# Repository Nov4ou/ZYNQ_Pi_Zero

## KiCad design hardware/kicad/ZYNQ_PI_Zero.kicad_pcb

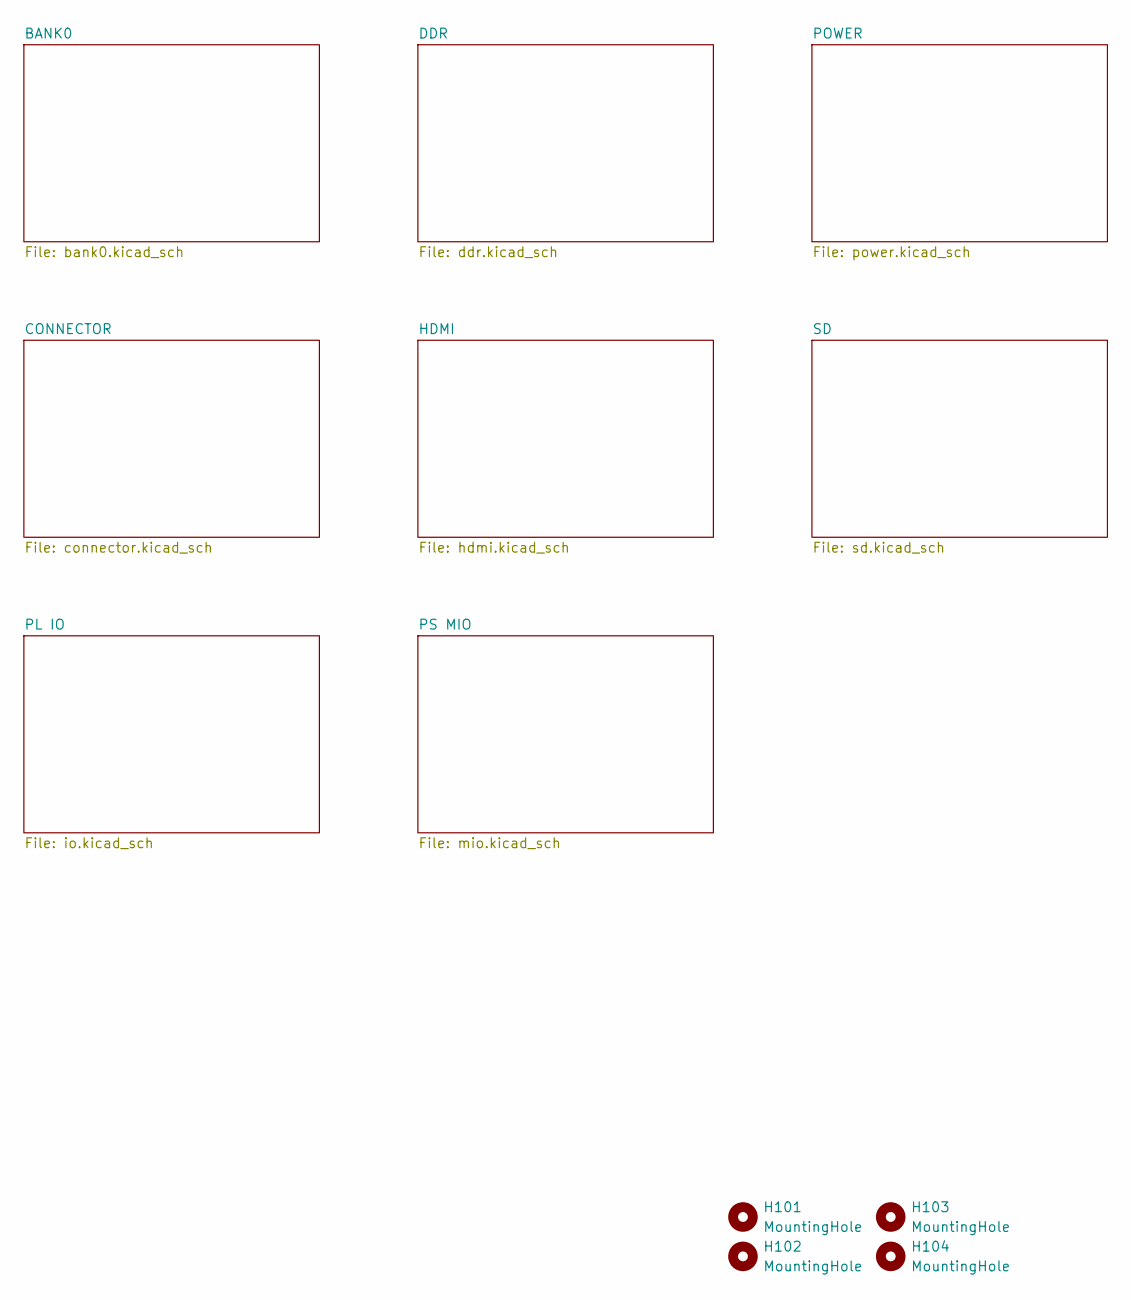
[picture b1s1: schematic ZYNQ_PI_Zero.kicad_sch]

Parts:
H101, H102, H103, H104: MountingHole; MountingHole_3.2mm_M3

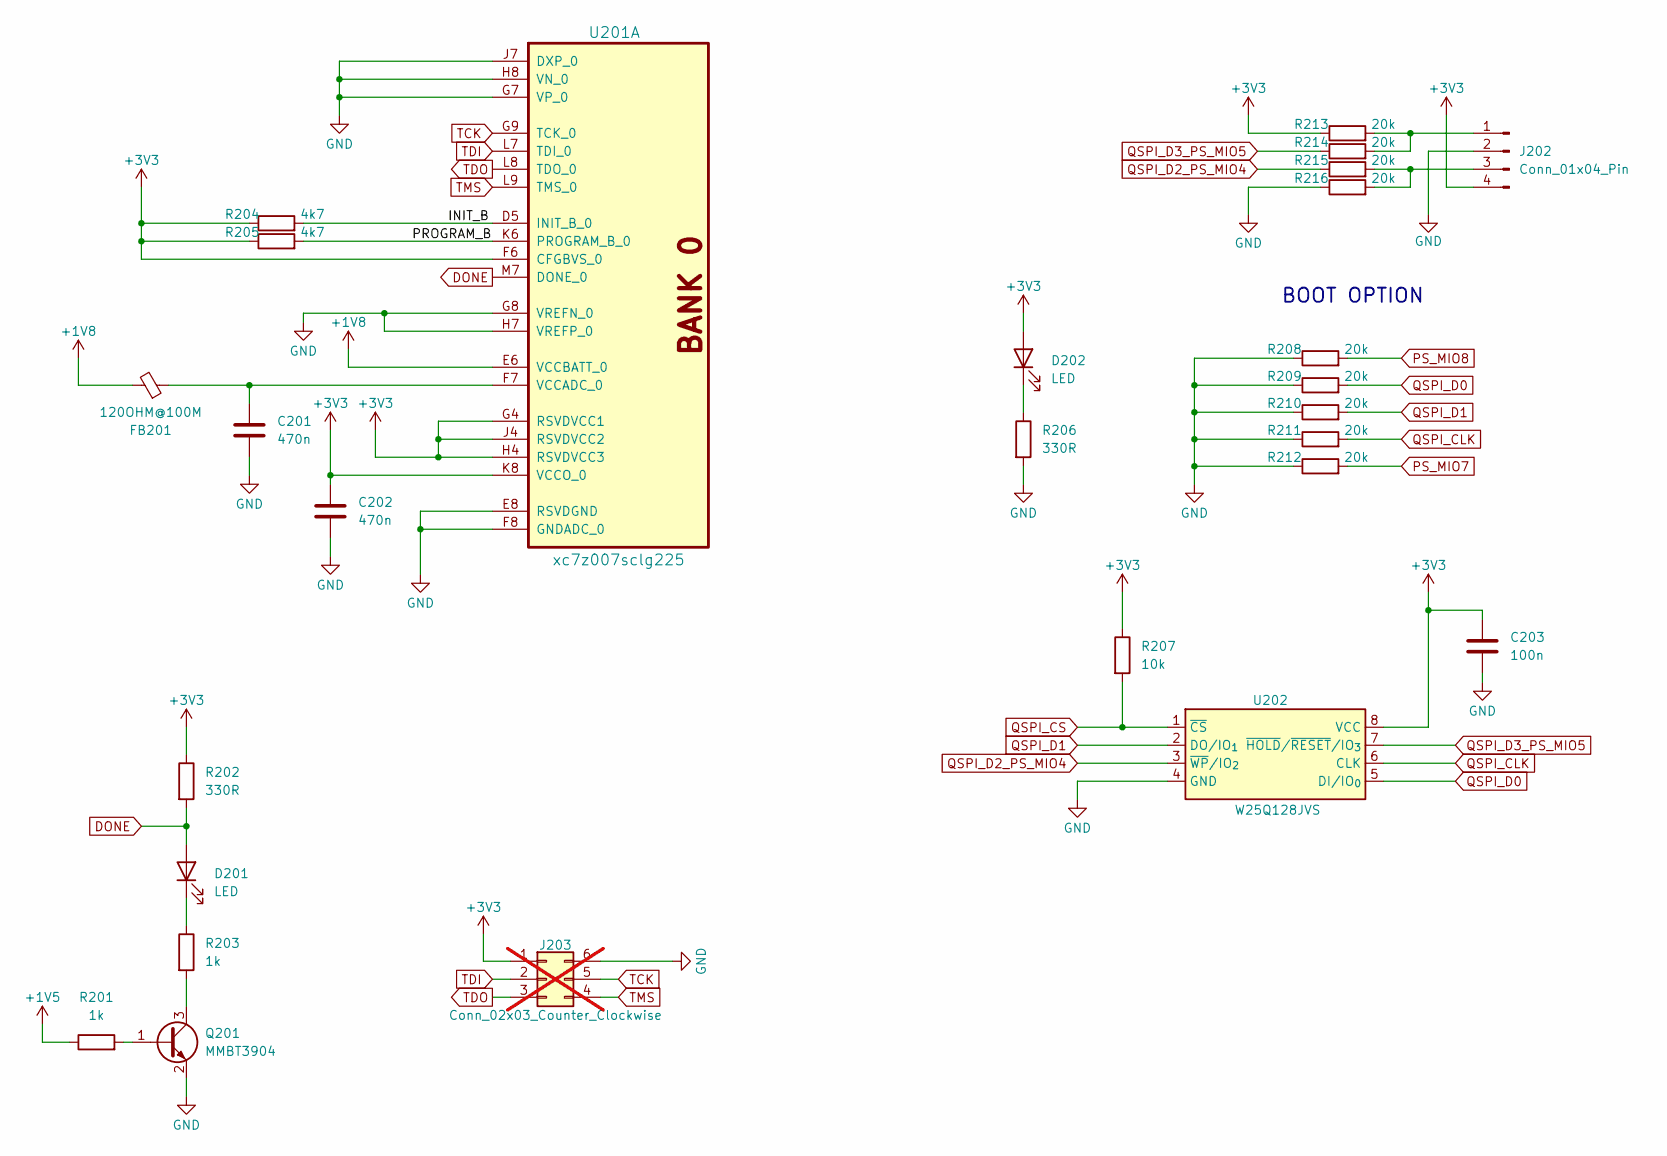
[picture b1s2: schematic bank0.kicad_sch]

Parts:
C201, C202: 470n; C_0402_1005Metric
C203: 100n; C_0402_1005Metric
D201, D202: LED; LED_0603_1608Metric
FB201: 120OHM@100M; L_0402_1005Metric
J202: Conn_01x04_Pin; PinHeader_1x04_P2.54mm_Vertical
J203: Conn_02x03_Counter_Clockwise; PinHeader_2x03_P2.00mm_Vertical; not fitted
Q201: MMBT3904; SOT-23
R201, R203: 1k; R_0402_1005Metric
R202, R206: 330R; R_0603_1608Metric
R204, R205: 4k7; R_0402_1005Metric
R207: 10k; R_0603_1608Metric
R208, R209, R210, R211, R212, R213, R214, R215, R216: 20k; R_0402_1005Metric
U201: xc7z007sclg225; Xilinx_CLG225
U202: W25Q128JVS; SOIC-8_5.3x5.3mm_P1.27mm

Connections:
+1V5: R201.1; also elsewhere on the board
+1V8: FB201.2, U201.E6 (VCCBATT_0); also elsewhere on the board
+3V3: C202.1, C203.1, D202.2 (A), J202.4, J203.1, R202.1, R204.1, R205.1, R207.1, R213.1, U201.F6 (CFGBVS_0), U201.G4 (RSVDVCC1), U201.H4 (RSVDVCC3), U201.J4 (RSVDVCC2), U201.K8 (VCCO_0), U202.8 (VCC); also elsewhere on the board
/BANK0/INIT_B: R204.2, U201.D5 (INIT_B_0)
/BANK0/PROGRAM_B: R205.2, U201.K6 (PROGRAM_B_0)
DONE: D201.2 (A), R202.2, U201.M7 (DONE_0)
GND: C201.2, C202.2, C203.2, J202.2, J203.6, Q201.2 (E), R206.2, R208.1, R209.1, R210.1, R211.1, R212.1, R216.1, U201.E8 (RSVDGND), U201.F8 (GNDADC_0), U201.G7 (VP_0), U201.G8 (VREFN_0), U201.H7 (VREFP_0), U201.H8 (VN_0), U201.J7 (DXP_0), U202.4 (GND); also elsewhere on the board
unnamed: D201.1 (K), R203.1
unnamed: D202.1 (K), R206.1
unnamed: J202.1, R213.2, R214.2
unnamed: J202.3, R215.2, R216.2
unnamed: Q201.1 (B), R201.2
unnamed: Q201.3 (C), R203.2
unnamed: C201.1, FB201.1, U201.F7 (VCCADC_0)
PS_MIO7: R212.2; also elsewhere on the board
PS_MIO8: R208.2; also elsewhere on the board
QSPI_CLK: R211.2, U202.6 (CLK); also elsewhere on the board
QSPI_CS: R207.2, U202.1 (~CS); also elsewhere on the board
QSPI_D0: R209.2, U202.5 (DI/IO_{0}); also elsewhere on the board
QSPI_D1: R210.2, U202.2 (DO/IO_{1}); also elsewhere on the board
QSPI_D2_PS_MIO4: R215.1, U202.3 (~WP/IO_{2}); also elsewhere on the board
QSPI_D3_PS_MIO5: R214.1, U202.7 (~HOLD/~RESET/IO_{3}); also elsewhere on the board
TCK: J203.5, U201.G9 (TCK_0)
TDI: J203.2, U201.L7 (TDI_0)
TDO: J203.3, U201.L8 (TDO_0)
TMS: J203.4, U201.L9 (TMS_0)

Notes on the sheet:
BOOT OPTION

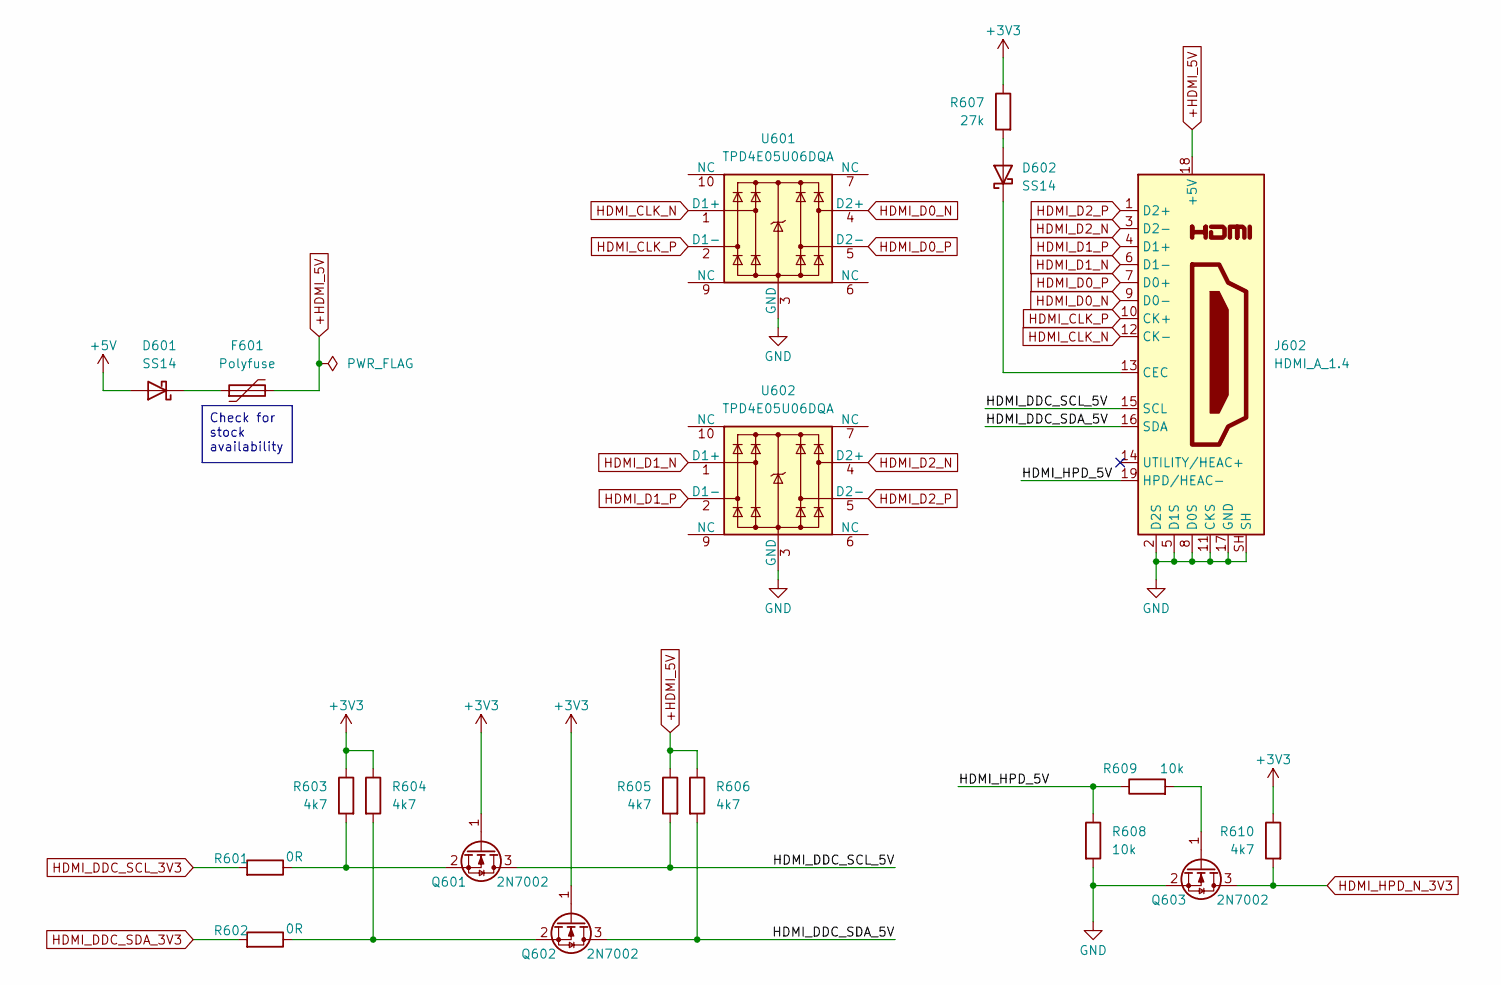
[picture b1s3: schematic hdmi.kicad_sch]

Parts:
D601, D602: SS14; D_SMA
F601: Polyfuse; Fuse_0805_2012Metric
J602: HDMI_A_1.4; HDMI-SMD_HDMI-19PIN-043_C2858275
Q601, Q602, Q603: 2N7002; SOT-23
R601, R602: 0R; R_0402_1005Metric
R603, R604, R605, R606, R610: 4k7; R_0402_1005Metric
R607: 27k; R_0603_1608Metric
R608, R609: 10k; R_0603_1608Metric
U601, U602: TPD4E05U06DQA; USON-10_2.5x1.0mm_P0.5mm

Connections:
+3V3: Q601.1 (G), Q602.1 (G), R603.1, R604.1, R607.1, R610.1; also elsewhere on the board
+5V: D601.2 (A); also elsewhere on the board
+HDMI_5V: F601.2, J602.18 (+5V), R605.1, R606.1
/HDMI/HDMI_DDC_SCL_5V: J602.15 (SCL), Q601.3 (D), R605.2
/HDMI/HDMI_DDC_SDA_5V: J602.16 (SDA), Q602.3 (D), R606.2
/HDMI/HDMI_HPD_5V: J602.19 (HPD/HEAC-), R608.1, R609.1
GND: J602.2 (D2S), J602.5 (D1S), J602.8 (D0S), J602.11 (CKS), J602.17 (GND), J602.SH, Q603.2 (S), R608.2, U601.3 (GND), U601.8 (GND), U602.3 (GND), U602.8 (GND); also elsewhere on the board
HDMI_CLK_N: J602.12 (CK-), U601.1 (D1+); also elsewhere on the board
HDMI_CLK_P: J602.10 (CK+), U601.2 (D1-); also elsewhere on the board
HDMI_D0_N: J602.9 (D0-), U601.4 (D2+); also elsewhere on the board
HDMI_D0_P: J602.7 (D0+), U601.5 (D2-); also elsewhere on the board
HDMI_D1_N: J602.6 (D1-), U602.1 (D1+); also elsewhere on the board
HDMI_D1_P: J602.4 (D1+), U602.2 (D1-); also elsewhere on the board
HDMI_D2_N: J602.3 (D2-), U602.4 (D2+); also elsewhere on the board
HDMI_D2_P: J602.1 (D2+), U602.5 (D2-); also elsewhere on the board
HDMI_DDC_SCL_3V3: R601.2; also elsewhere on the board
HDMI_DDC_SDA_3V3: R602.2; also elsewhere on the board
HDMI_HPD_N_3V3: Q603.3 (D), R610.2; also elsewhere on the board
unnamed: D601.1 (K), F601.1
unnamed: D602.2 (A), R607.2
unnamed: D602.1 (K), J602.13 (CEC)
unnamed: Q601.2 (S), R601.1, R603.2
unnamed: Q602.2 (S), R602.1, R604.2
unnamed: Q603.1 (G), R609.2

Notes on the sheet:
Check for stock availability

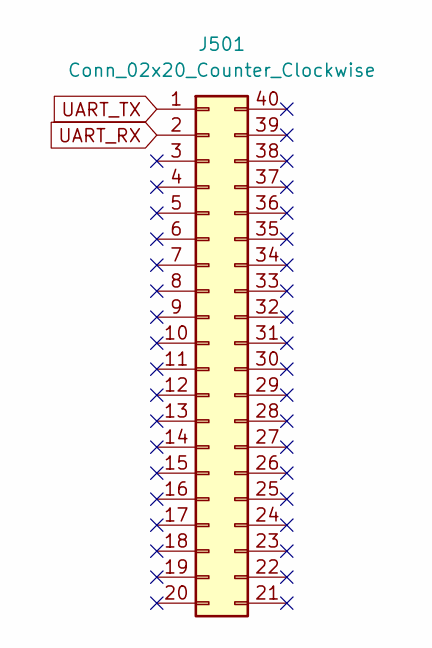
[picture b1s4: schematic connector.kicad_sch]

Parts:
J501: Conn_02x20_Counter_Clockwise; PinHeader_2x20_P2.54mm_Vertical

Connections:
UART_RX: J501.2; also elsewhere on the board
UART_TX: J501.1; also elsewhere on the board

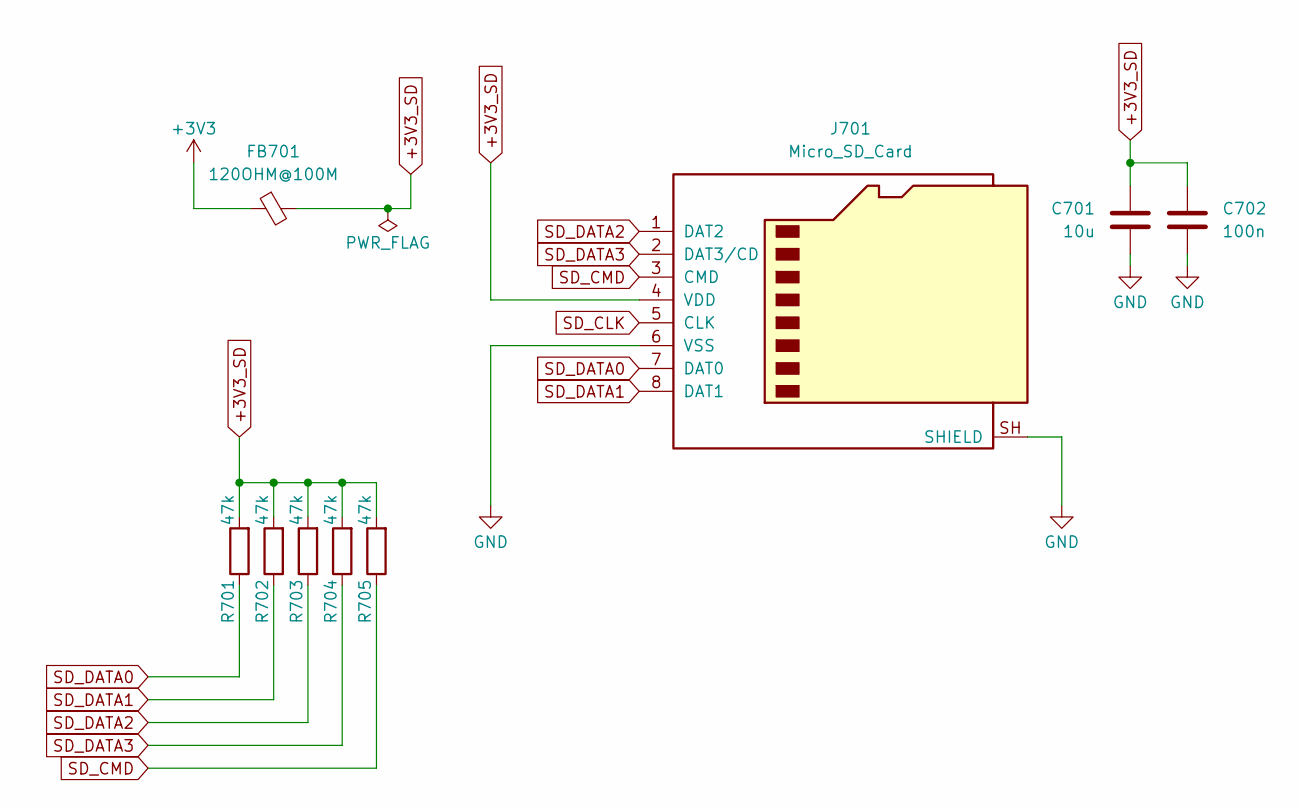
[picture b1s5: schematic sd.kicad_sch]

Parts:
C701: 10u; C_0603_1608Metric
C702: 100n; C_0402_1005Metric
FB701: 120OHM@100M; L_0402_1005Metric
J701: Micro_SD_Card; TF-SMD_TF-115-BCP9_LARG
R701, R702, R703, R704, R705: 47k; R_0402_1005Metric

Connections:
+3V3: FB701.1; also elsewhere on the board
+3V3_SD: C701.1, C702.1, FB701.2, J701.4 (VDD), R701.2, R702.2, R703.2, R704.2, R705.2
GND: C701.2, C702.2, J701.6 (VSS), J701.SH (SHIELD); also elsewhere on the board
SD_CLK: J701.5 (CLK); also elsewhere on the board
SD_CMD: J701.3 (CMD), R705.1; also elsewhere on the board
SD_DATA0: J701.7 (DAT0), R701.1; also elsewhere on the board
SD_DATA1: J701.8 (DAT1), R702.1; also elsewhere on the board
SD_DATA2: J701.1 (DAT2), R703.1; also elsewhere on the board
SD_DATA3: J701.2 (DAT3/CD), R704.1; also elsewhere on the board

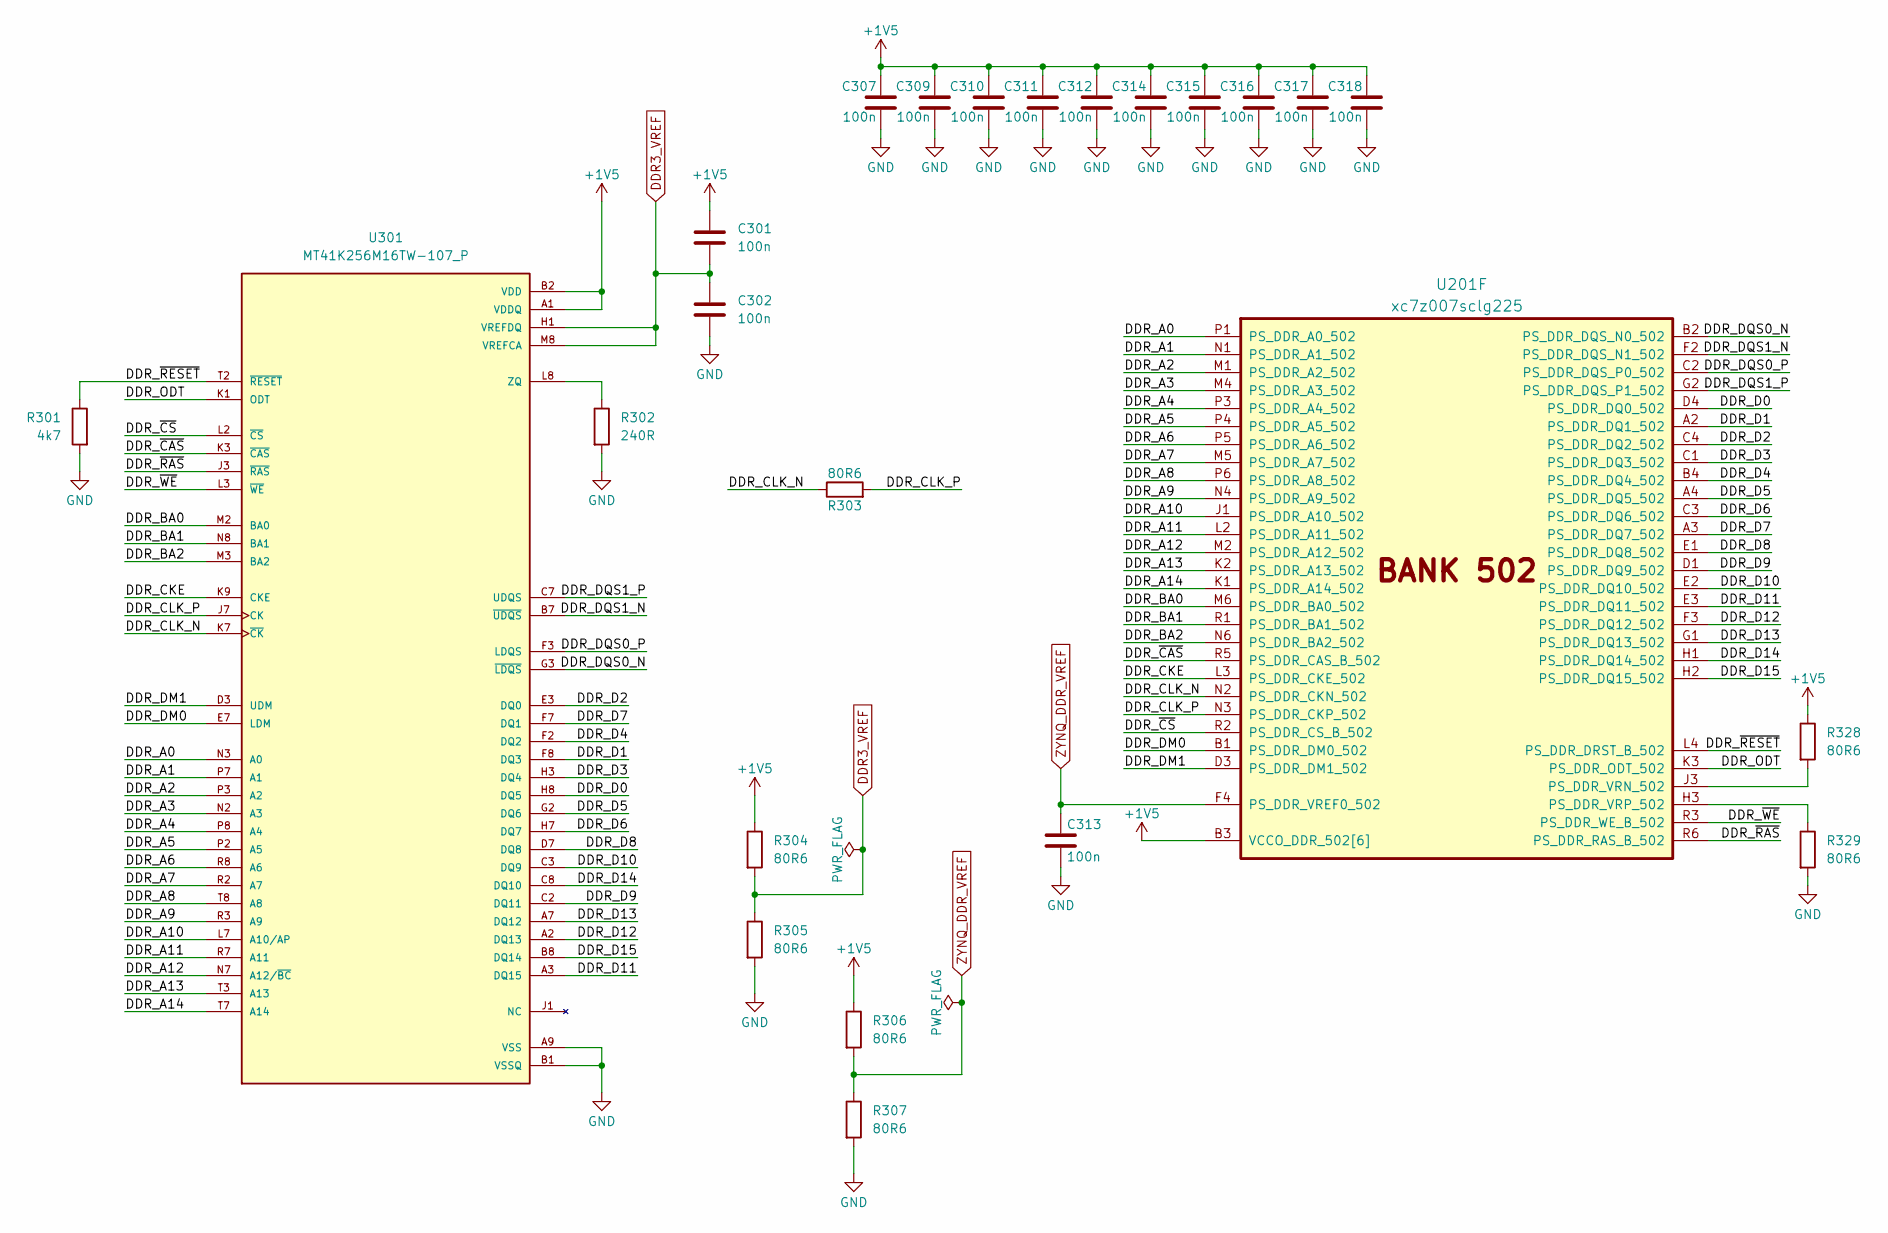
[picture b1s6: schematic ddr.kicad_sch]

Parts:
C301, C302, C307, C309, C310, C311, C312, C313, C314, C315, C316, C317, C318: 100n; C_0402_1005Metric
R301: 4k7; R_0402_1005Metric
R302: 240R; R_0402_1005Metric
R303, R304, R305, R306, R307, R328, R329: 80R6; R_0402_1005Metric
U201: xc7z007sclg225
U301: MT41K256M16TW-107_P; BGA96C80P9X16_1400X800X120; PARTREV P

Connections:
+1V5: C301.1, C307.1, C309.1, C310.1, C311.1, C312.1, C314.1, C315.1, C316.1, C317.1, C318.1, R304.1, R306.1, R328.1, U201.B3 (VCCO_DDR_502[6]), U201.E4 (VCCO_DDR_502[6]), U201.F1 (VCCO_DDR_502[6]), U201.J2 (VCCO_DDR_502[6]), U201.M3 (VCCO_DDR_502[6]), U201.R4 (VCCO_DDR_502[6]), U301.A1 (VDDQ), U301.A8 (VDDQ), U301.B2 (VDD), U301.C1 (VDDQ), U301.C9 (VDDQ), U301.D2 (VDDQ), U301.D9 (VDD), U301.E9 (VDDQ), U301.F1 (VDDQ), U301.G7 (VDD), U301.H2 (VDDQ), U301.H9 (VDDQ), U301.K2 (VDD), U301.K8 (VDD), U301.N1 (VDD), U301.N9 (VDD), U301.R1 (VDD), U301.R9 (VDD); also elsewhere on the board
/DDR/DDR_A0: U201.P1 (PS_DDR_A0_502), U301.N3 (A0)
/DDR/DDR_A1: U201.N1 (PS_DDR_A1_502), U301.P7 (A1)
/DDR/DDR_A2: U201.M1 (PS_DDR_A2_502), U301.P3 (A2)
/DDR/DDR_A3: U201.M4 (PS_DDR_A3_502), U301.N2 (A3)
/DDR/DDR_A4: U201.P3 (PS_DDR_A4_502), U301.P8 (A4)
/DDR/DDR_A5: U201.P4 (PS_DDR_A5_502), U301.P2 (A5)
/DDR/DDR_A6: U201.P5 (PS_DDR_A6_502), U301.R8 (A6)
/DDR/DDR_A7: U201.M5 (PS_DDR_A7_502), U301.R2 (A7)
/DDR/DDR_A8: U201.P6 (PS_DDR_A8_502), U301.T8 (A8)
/DDR/DDR_A9: U201.N4 (PS_DDR_A9_502), U301.R3 (A9)
/DDR/DDR_A10: U201.J1 (PS_DDR_A10_502), U301.L7 (A10/AP)
/DDR/DDR_A11: U201.L2 (PS_DDR_A11_502), U301.R7 (A11)
/DDR/DDR_A12: U201.M2 (PS_DDR_A12_502), U301.N7 (A12/~BC)
/DDR/DDR_A13: U201.K2 (PS_DDR_A13_502), U301.T3 (A13)
/DDR/DDR_A14: U201.K1 (PS_DDR_A14_502), U301.T7 (A14)
/DDR/DDR_BA0: U201.M6 (PS_DDR_BA0_502), U301.M2 (BA0)
/DDR/DDR_BA1: U201.R1 (PS_DDR_BA1_502), U301.N8 (BA1)
/DDR/DDR_BA2: U201.N6 (PS_DDR_BA2_502), U301.M3 (BA2)
/DDR/DDR_CKE: U201.L3 (PS_DDR_CKE_502), U301.K9 (CKE)
/DDR/DDR_CLK_N: R303.1, U201.N2 (PS_DDR_CKN_502), U301.K7 (~CK)
/DDR/DDR_CLK_P: R303.2, U201.N3 (PS_DDR_CKP_502), U301.J7 (CK)
/DDR/DDR_D0: U201.D4 (PS_DDR_DQ0_502), U301.H8 (DQ5)
/DDR/DDR_D1: U201.A2 (PS_DDR_DQ1_502), U301.F8 (DQ3)
/DDR/DDR_D2: U201.C4 (PS_DDR_DQ2_502), U301.E3 (DQ0)
/DDR/DDR_D3: U201.C1 (PS_DDR_DQ3_502), U301.H3 (DQ4)
/DDR/DDR_D4: U201.B4 (PS_DDR_DQ4_502), U301.F2 (DQ2)
/DDR/DDR_D5: U201.A4 (PS_DDR_DQ5_502), U301.G2 (DQ6)
/DDR/DDR_D6: U201.C3 (PS_DDR_DQ6_502), U301.H7 (DQ7)
/DDR/DDR_D7: U201.A3 (PS_DDR_DQ7_502), U301.F7 (DQ1)
/DDR/DDR_D8: U201.E1 (PS_DDR_DQ8_502), U301.D7 (DQ8)
/DDR/DDR_D9: U201.D1 (PS_DDR_DQ9_502), U301.C2 (DQ11)
/DDR/DDR_D10: U201.E2 (PS_DDR_DQ10_502), U301.C3 (DQ9)
/DDR/DDR_D11: U201.E3 (PS_DDR_DQ11_502), U301.A3 (DQ15)
/DDR/DDR_D12: U201.F3 (PS_DDR_DQ12_502), U301.A2 (DQ13)
/DDR/DDR_D13: U201.G1 (PS_DDR_DQ13_502), U301.A7 (DQ12)
/DDR/DDR_D14: U201.H1 (PS_DDR_DQ14_502), U301.C8 (DQ10)
/DDR/DDR_D15: U201.H2 (PS_DDR_DQ15_502), U301.B8 (DQ14)
/DDR/DDR_DM0: U201.B1 (PS_DDR_DM0_502), U301.E7 (LDM)
/DDR/DDR_DM1: U201.D3 (PS_DDR_DM1_502), U301.D3 (UDM)
/DDR/DDR_DQS0_N: U201.B2 (PS_DDR_DQS_N0_502), U301.G3 (~LDQS)
/DDR/DDR_DQS0_P: U201.C2 (PS_DDR_DQS_P0_502), U301.F3 (LDQS)
/DDR/DDR_DQS1_N: U201.F2 (PS_DDR_DQS_N1_502), U301.B7 (~UDQS)
/DDR/DDR_DQS1_P: U201.G2 (PS_DDR_DQS_P1_502), U301.C7 (UDQS)
/DDR/DDR_ODT: U201.K3 (PS_DDR_ODT_502), U301.K1 (ODT)
/DDR/DDR_~CAS: U201.R5 (PS_DDR_CAS_B_502), U301.K3 (~CAS)
/DDR/DDR_~CS: U201.R2 (PS_DDR_CS_B_502), U301.L2 (~CS)
/DDR/DDR_~RAS: U201.R6 (PS_DDR_RAS_B_502), U301.J3 (~RAS)
/DDR/DDR_~RESET: R301.1, U201.L4 (PS_DDR_DRST_B_502), U301.T2 (~RESET)
/DDR/DDR_~WE: U201.R3 (PS_DDR_WE_B_502), U301.L3 (~WE)
DDR3_VREF: C301.2, C302.1, R304.2, R305.1, U301.H1 (VREFDQ), U301.M8 (VREFCA)
GND: C302.2, C307.2, C309.2, C310.2, C311.2, C312.2, C313.2, C314.2, C315.2, C316.2, C317.2, C318.2, R301.2, R302.2, R305.2, R307.2, R329.2, U301.A9 (VSS), U301.B1 (VSSQ), U301.B3 (VSS), U301.B9 (VSSQ), U301.D1 (VSSQ), U301.D8 (VSSQ), U301.E1 (VSS), U301.E2 (VSSQ), U301.E8 (VSSQ), U301.F9 (VSSQ), U301.G1 (VSSQ), U301.G8 (VSS), U301.G9 (VSSQ), U301.J2 (VSS), U301.J8 (VSS), U301.M1 (VSS), U301.M9 (VSS), U301.P1 (VSS), U301.P9 (VSS), U301.T1 (VSS), U301.T9 (VSS); also elsewhere on the board
unnamed: R328.2, U201.J3 (PS_DDR_VRN_502)
unnamed: R329.1, U201.H3 (PS_DDR_VRP_502)
unnamed: R302.1, U301.L8 (ZQ)
ZYNQ_DDR_VREF: C313.1, R306.2, R307.1, U201.F4 (PS_DDR_VREF0_502)

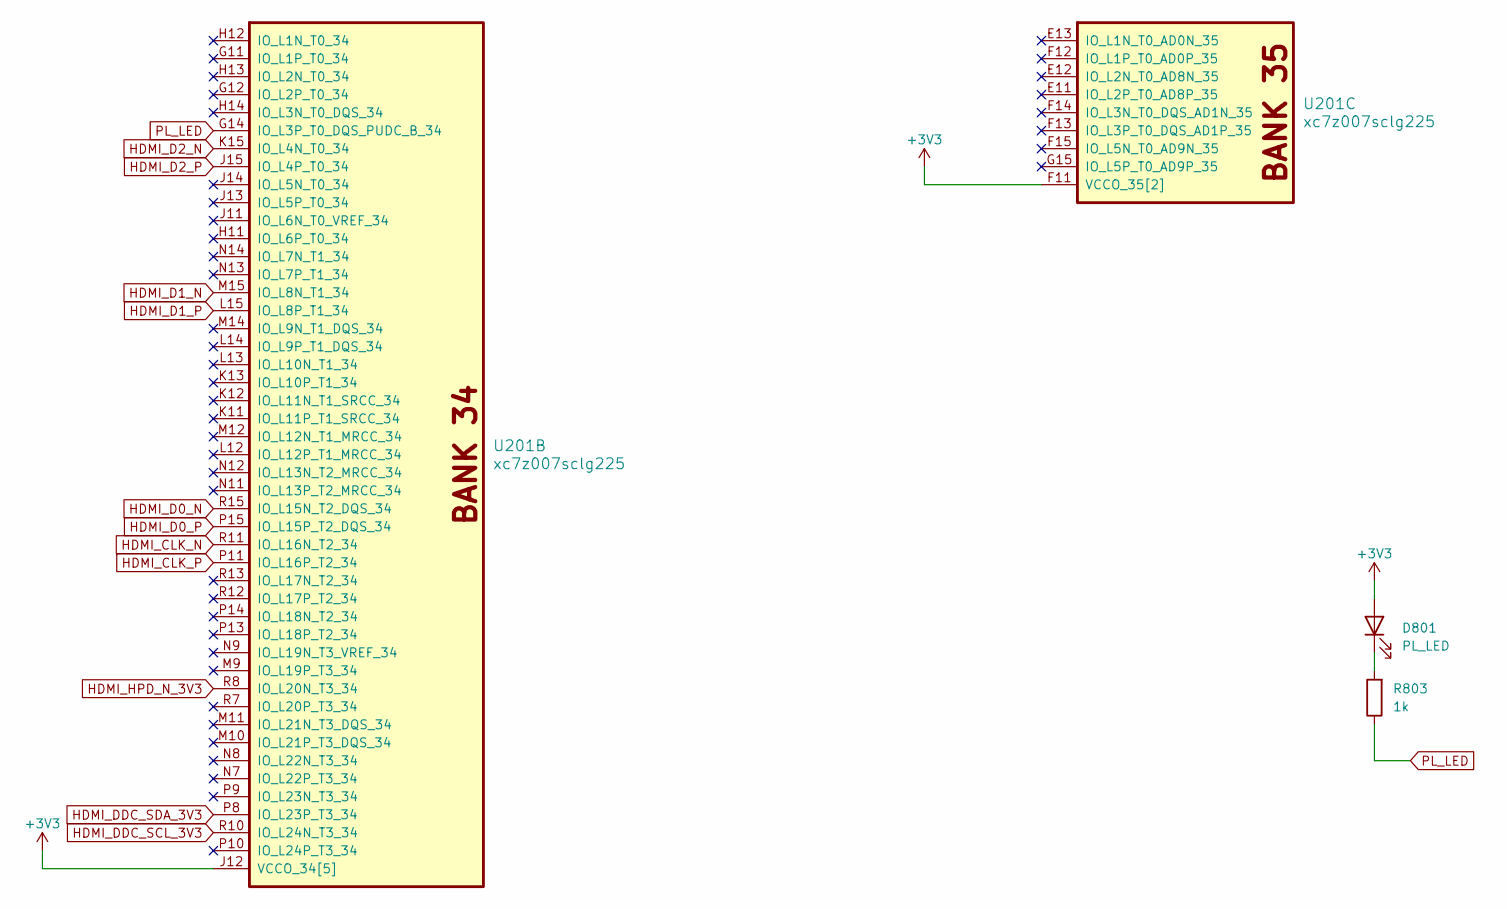
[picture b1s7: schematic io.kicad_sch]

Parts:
D801: PL_LED; LED_0603_1608Metric
R803: 1k; R_0402_1005Metric
U201: xc7z007sclg225

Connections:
+3V3: D801.2 (A), U201.F11 (VCCO_35[2]), U201.H15 (VCCO_35[2]), U201.J12 (VCCO_34[5]), U201.M13 (VCCO_34[5]), U201.N10 (VCCO_34[5]), U201.P7 (VCCO_34[5]), U201.R14 (VCCO_34[5]); also elsewhere on the board
HDMI_CLK_N: U201.R11 (IO_L16N_T2_34); also elsewhere on the board
HDMI_CLK_P: U201.P11 (IO_L16P_T2_34); also elsewhere on the board
HDMI_D0_N: U201.R15 (IO_L15N_T2_DQS_34); also elsewhere on the board
HDMI_D0_P: U201.P15 (IO_L15P_T2_DQS_34); also elsewhere on the board
HDMI_D1_N: U201.M15 (IO_L8N_T1_34); also elsewhere on the board
HDMI_D1_P: U201.L15 (IO_L8P_T1_34); also elsewhere on the board
HDMI_D2_N: U201.K15 (IO_L4N_T0_34); also elsewhere on the board
HDMI_D2_P: U201.J15 (IO_L4P_T0_34); also elsewhere on the board
HDMI_DDC_SCL_3V3: U201.R10 (IO_L24N_T3_34); also elsewhere on the board
HDMI_DDC_SDA_3V3: U201.P8 (IO_L23P_T3_34); also elsewhere on the board
HDMI_HPD_N_3V3: U201.R8 (IO_L20N_T3_34); also elsewhere on the board
unnamed: D801.1 (K), R803.2
PL_LED: R803.1, U201.G14 (IO_L3P_T0_DQS_PUDC_B_34)

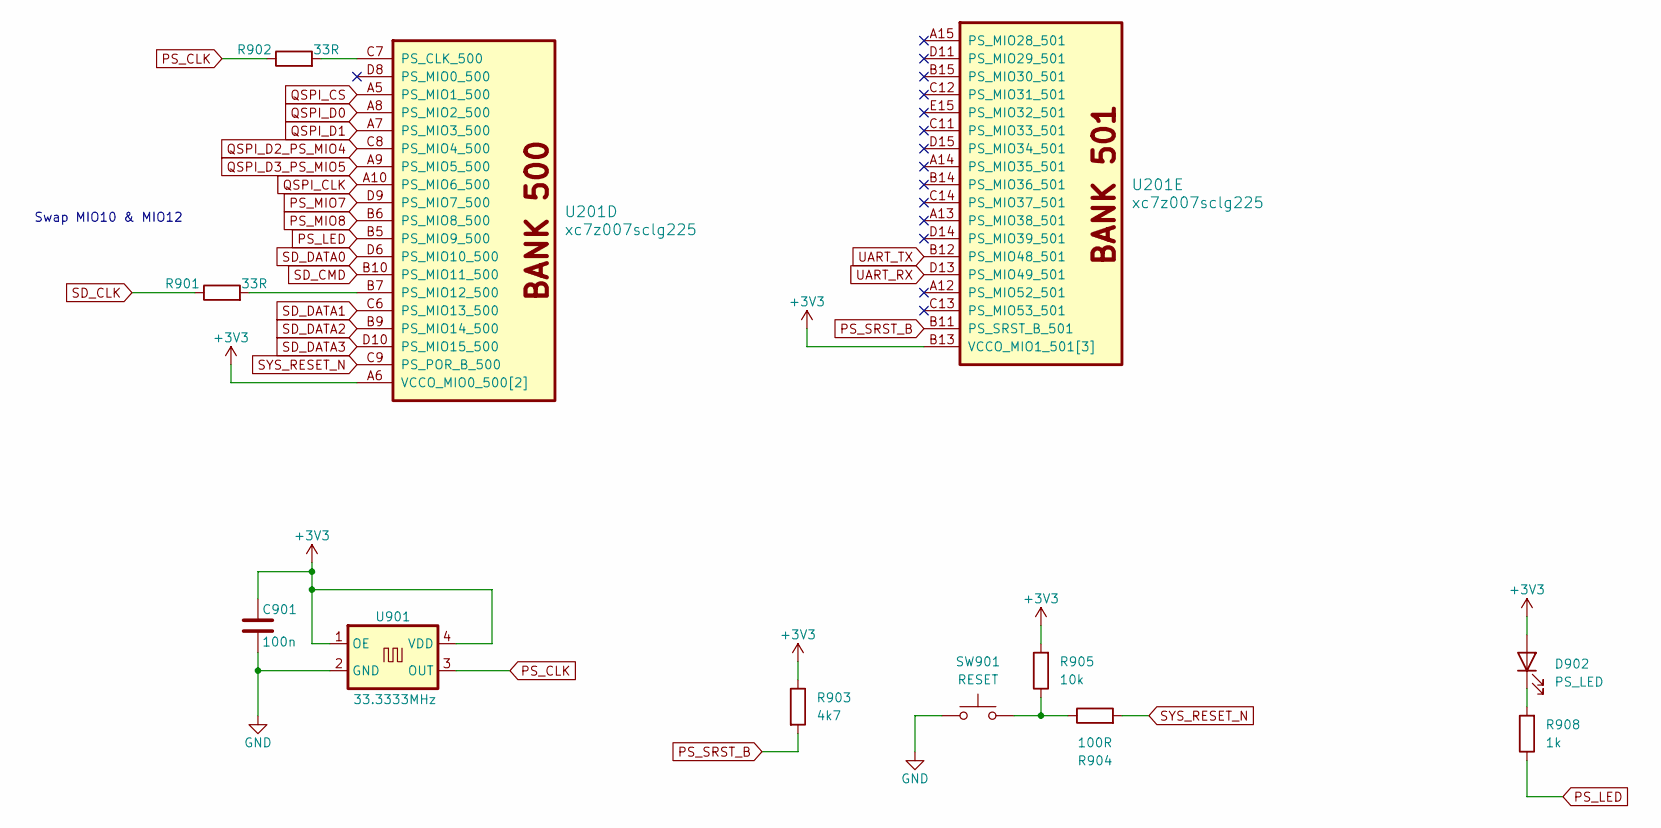
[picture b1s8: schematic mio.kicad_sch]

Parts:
C901: 100n; C_0402_1005Metric
D902: PS_LED; LED_0603_1608Metric
R901, R902: 33R; R_0603_1608Metric
R903: 4k7; R_0402_1005Metric
R904: 100R; R_0603_1608Metric
R905: 10k; R_0603_1608Metric
R908: 1k; R_0402_1005Metric
SW901: RESET; SW_Tactile_SPST_NO_Straight_CK_PTS636Sx25SMTRLFS
U201: xc7z007sclg225
U901: 33.3333MHz; Oscillator_SMD_SeikoEpson_SG8002CE-4Pin_3.2x2.5mm

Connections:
+3V3: C901.1, D902.2 (A), R903.1, R905.2, U201.A6 (VCCO_MIO0_500[2]), U201.B13 (VCCO_MIO1_501[3]), U201.C10 (VCCO_MIO1_501[3]), U201.D7 (VCCO_MIO0_500[2]), U201.E14 (VCCO_MIO1_501[3]), U901.1 (OE), U901.4 (VDD); also elsewhere on the board
GND: C901.2, SW901.1, U901.2 (GND); also elsewhere on the board
unnamed: D902.1 (K), R908.2
unnamed: R904.1, R905.1, SW901.2
unnamed: R902.2, U201.C7 (PS_CLK_500)
unnamed: R901.2, U201.B7 (PS_MIO12_500)
PS_CLK: R902.1, U901.3 (OUT)
PS_LED: R908.1, U201.B5 (PS_MIO9_500)
PS_MIO7: U201.D9 (PS_MIO7_500); also elsewhere on the board
PS_MIO8: U201.B6 (PS_MIO8_500); also elsewhere on the board
PS_SRST_B: R903.2, U201.B11 (PS_SRST_B_501)
QSPI_CLK: U201.A10 (PS_MIO6_500); also elsewhere on the board
QSPI_CS: U201.A5 (PS_MIO1_500); also elsewhere on the board
QSPI_D0: U201.A8 (PS_MIO2_500); also elsewhere on the board
QSPI_D1: U201.A7 (PS_MIO3_500); also elsewhere on the board
QSPI_D2_PS_MIO4: U201.C8 (PS_MIO4_500); also elsewhere on the board
QSPI_D3_PS_MIO5: U201.A9 (PS_MIO5_500); also elsewhere on the board
SD_CLK: R901.1; also elsewhere on the board
SD_CMD: U201.B10 (PS_MIO11_500); also elsewhere on the board
SD_DATA0: U201.D6 (PS_MIO10_500); also elsewhere on the board
SD_DATA1: U201.C6 (PS_MIO13_500); also elsewhere on the board
SD_DATA2: U201.B9 (PS_MIO14_500); also elsewhere on the board
SD_DATA3: U201.D10 (PS_MIO15_500); also elsewhere on the board
SYS_RESET_N: R904.2, U201.C9 (PS_POR_B_500)
UART_RX: U201.D13 (PS_MIO49_501); also elsewhere on the board
UART_TX: U201.B12 (PS_MIO48_501); also elsewhere on the board

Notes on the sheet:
Swap MIO10 & MIO12

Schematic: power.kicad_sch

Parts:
C401, C402, C409, C410, C411, C418, C420, C423, C431, C452: 10u; C_0603_1608Metric
C403, C404, C414, C417, C461, C462: 100n; C_0402_1005Metric
C405, C406, C416: 3n3; C_0402_1005Metric
C407, C408, C426: 22u; C_0603_1608Metric
C413, C422, C429, C430, C432, C442, C445, C446, C447, C449, C450, C451, C454, C455, C457, C458, C459, C460: 470n; C_0402_1005Metric
C419, C425, C428, C437, C439, C440, C441, C444, C448, C453, C456: 4u7; C_0603_1608Metric
C434, C436: 100u; C_1206_3216Metric
FB401: 120OHM@100M; L_0402_1005Metric
J401: USB_C_Receptacle_USB2.0_16P; USB_C_Receptacle_GCT_USB4105-xx-A_16P_TopMnt_Horizontal
L401, L402, L403: CMLB041B-2R2MS; IND_CMLB041B-1R0MS
R401, R402: 5k1; R_0603_1608Metric
R403, R404, R409: 100k; R_0402_1005Metric
R405: 49.9k; R_0402_1005Metric
R406: 200k; R_0402_1005Metric
R407: 13k; R_0402_1005Metric
R408, R411: 15k; R_0402_1005Metric
R410: 18k7; R_0402_1005Metric
U201: xc7z007sclg225
U401, U402, U405: TPS62130ARGTR; QFN50P300X300X100-17N-D; Manufacturer_Part_Number TPS62130ARGTR; Mouser Part Number 595-TPS62130ARGTR
U403: SPX3819M5-L-3-3; MPN SPX3819M5-L-3-3

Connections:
+1V0: C407.1, C420.1, C423.1, C425.1, C428.1, C429.1, C430.1, C432.1, C444.1, C448.1, C454.1, C458.1, C462.1, L401.2, R405.1, U201.E10 (VCCINT[5]), U201.F9 (VCCINT[5]), U201.G6 (VCCPINT[3]), U201.G10 (VCCINT[5]), U201.H5 (VCCPINT[3]), U201.J10 (VCCINT[5]), U201.K5 (VCCPINT[3]), U201.L10 (VCCINT[5]), U401.14 (VOS)
+1V5: C408.1, C436.1, C441.1, C447.1, C451.1, C455.1, C459.1, L402.2, R407.1, U402.14 (VOS); also elsewhere on the board
+1V8: C419.1, C422.1, C426.1, C452.1, C453.1, C456.1, C457.1, C460.1, C461.1, FB401.2, L403.2, R410.1, U201.H9 (VCCAUX[3]), U201.J6 (VCCPAUX[2]), U201.J8 (VCCAUX[3]), U201.K9 (VCCAUX[3]), U201.L6 (VCCPAUX[2]), U405.14 (VOS); also elsewhere on the board
+3V3: C417.1, C418.1, C431.1, C434.1, C437.1, C439.1, C440.1, C442.1, C445.1, C446.1, C449.1, C450.1, U403.5 (VOUT); also elsewhere on the board
+5V: C401.1, C402.1, C403.1, C404.1, C409.1, C411.1, C414.1, J401.A4 (VBUS), J401.A9 (VBUS), J401.B4 (VBUS), J401.B9 (VBUS), R403.1, R404.1, R409.1, U401.10 (AVIN), U401.11 (PVIN_1), U401.12 (PVIN_2), U401.13 (EN), U402.10 (AVIN), U402.11 (PVIN_1), U402.12 (PVIN_2), U403.1 (VIN), U405.10 (AVIN), U405.11 (PVIN_1), U405.12 (PVIN_2); also elsewhere on the board
/POWER/1V0_PG: R403.2, U401.4 (PG), U405.13 (EN)
/POWER/1V0_SW: L401.1, U401.1 (SW_1), U401.2 (SW_2), U401.3 (SW_3)
/POWER/1V5_PG: R404.2, U402.4 (PG), U403.3 (EN)
/POWER/1V5_SW: L402.1, U402.1 (SW_1), U402.2 (SW_2), U402.3 (SW_3)
/POWER/1V8_PG: R409.2, U402.13 (EN), U405.4 (PG)
/POWER/1V8_SW: L403.1, U405.1 (SW_1), U405.2 (SW_2), U405.3 (SW_3)
GND: C401.2, C402.2, C403.2, C404.2, C405.1, C406.1, C407.2, C408.2, C409.2, C410.2, C411.2, C413.2, C414.2, C416.1, C417.2, C418.2, C419.2, C420.2, C422.2, C423.2, C425.2, C426.2, C428.2, C429.2, C430.2, C431.2, C432.2, C434.2, C436.2, C437.2, C439.2, C440.2, C441.2, C442.2, C444.2, C445.2, C446.2, C447.2, C448.2, C449.2, C450.2, C451.2, C452.2, C453.2, C454.2, C455.2, C456.2, C457.2, C458.2, C459.2, C460.2, C461.2, C462.2, J401.A1 (GND), J401.A12 (GND), J401.B1 (GND), J401.B12 (GND), J401.SH (SHIELD), R401.2, R402.2, R406.2, R408.2, R411.2, U201.A1 (GND[31]), U201.A11 (GND[31]), U201.B8 (GND[31]), U201.C5 (GND[31]), U201.C15 (GND[31]), U201.D2 (GND[31]), U201.D12 (GND[31]), U201.E5 (GND[31]), U201.E7 (GND[31]), U201.E9 (GND[31]), U201.F10 (GND[31]), U201.G3 (GND[31]), U201.G5 (GND[31]), U201.G13 (GND[31]), U201.H6 (GND[31]), U201.H10 (GND[31]), U201.J5 (GND[31]), U201.J9 (GND[31]), U201.K4 (GND[31]), U201.K7 (GND[31]), U201.K10 (GND[31]), U201.K14 (GND[31]), U201.L1 (GND[31]), U201.L5 (GND[31]), U201.L11 (GND[31]), U201.M8 (GND[31]), U201.N5 (GND[31]), U201.N15 (GND[31]), U201.P2 (GND[31]), U201.P12 (GND[31]), U201.R9 (GND[31]), U401.6 (AGND), U401.7 (FSW), U401.8 (DEF), U401.15 (PGND_1), U401.16 (PGND_2), U401.17 (EP), U402.6 (AGND), U402.7 (FSW), U402.8 (DEF), U402.15 (PGND_1), U402.16 (PGND_2), U402.17 (EP), U403.2 (GND), U405.6 (AGND), U405.7 (FSW), U405.8 (DEF), U405.15 (PGND_1), U405.16 (PGND_2), U405.17 (EP); also elsewhere on the board
unnamed: J401.A5 (CC1), R402.1
unnamed: J401.B5 (CC2), R401.1
unnamed: C410.1, C413.1, FB401.1, U201.F5 (VCCPLL)
unnamed: R405.2, R406.1, U401.5 (FB)
unnamed: C405.2, U401.9 (SS/TR)
unnamed: R407.2, R408.1, U402.5 (FB)
unnamed: C406.2, U402.9 (SS/TR)
unnamed: R410.2, R411.1, U405.5 (FB)
unnamed: C416.2, U405.9 (SS/TR)

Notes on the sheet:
VCC_PINT
VCCO_DDR_502
VCCIO 34
VCCO_MIO_500
VCC_PAUX
VCCO_MIO_501
VCC_AUX
VCCIO 35
VCC_BRAM
VCCINT
